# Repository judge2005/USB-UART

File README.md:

# USB-UART
A USB to serial adapter specifically designed for programming the ESP01. It uses node-mcu style programming, so no fiddling with buttons is necessary - just change the reset method to 'node-mcu'.

It has enough power to run the ESP01 without the need for an additional power source.

It uses the Silicon Labs CP2102N, so it can detect the charge protocol supported by the USB port it is plugged in to. You will have to use the Silicon Labs Express Configurator to set that up.

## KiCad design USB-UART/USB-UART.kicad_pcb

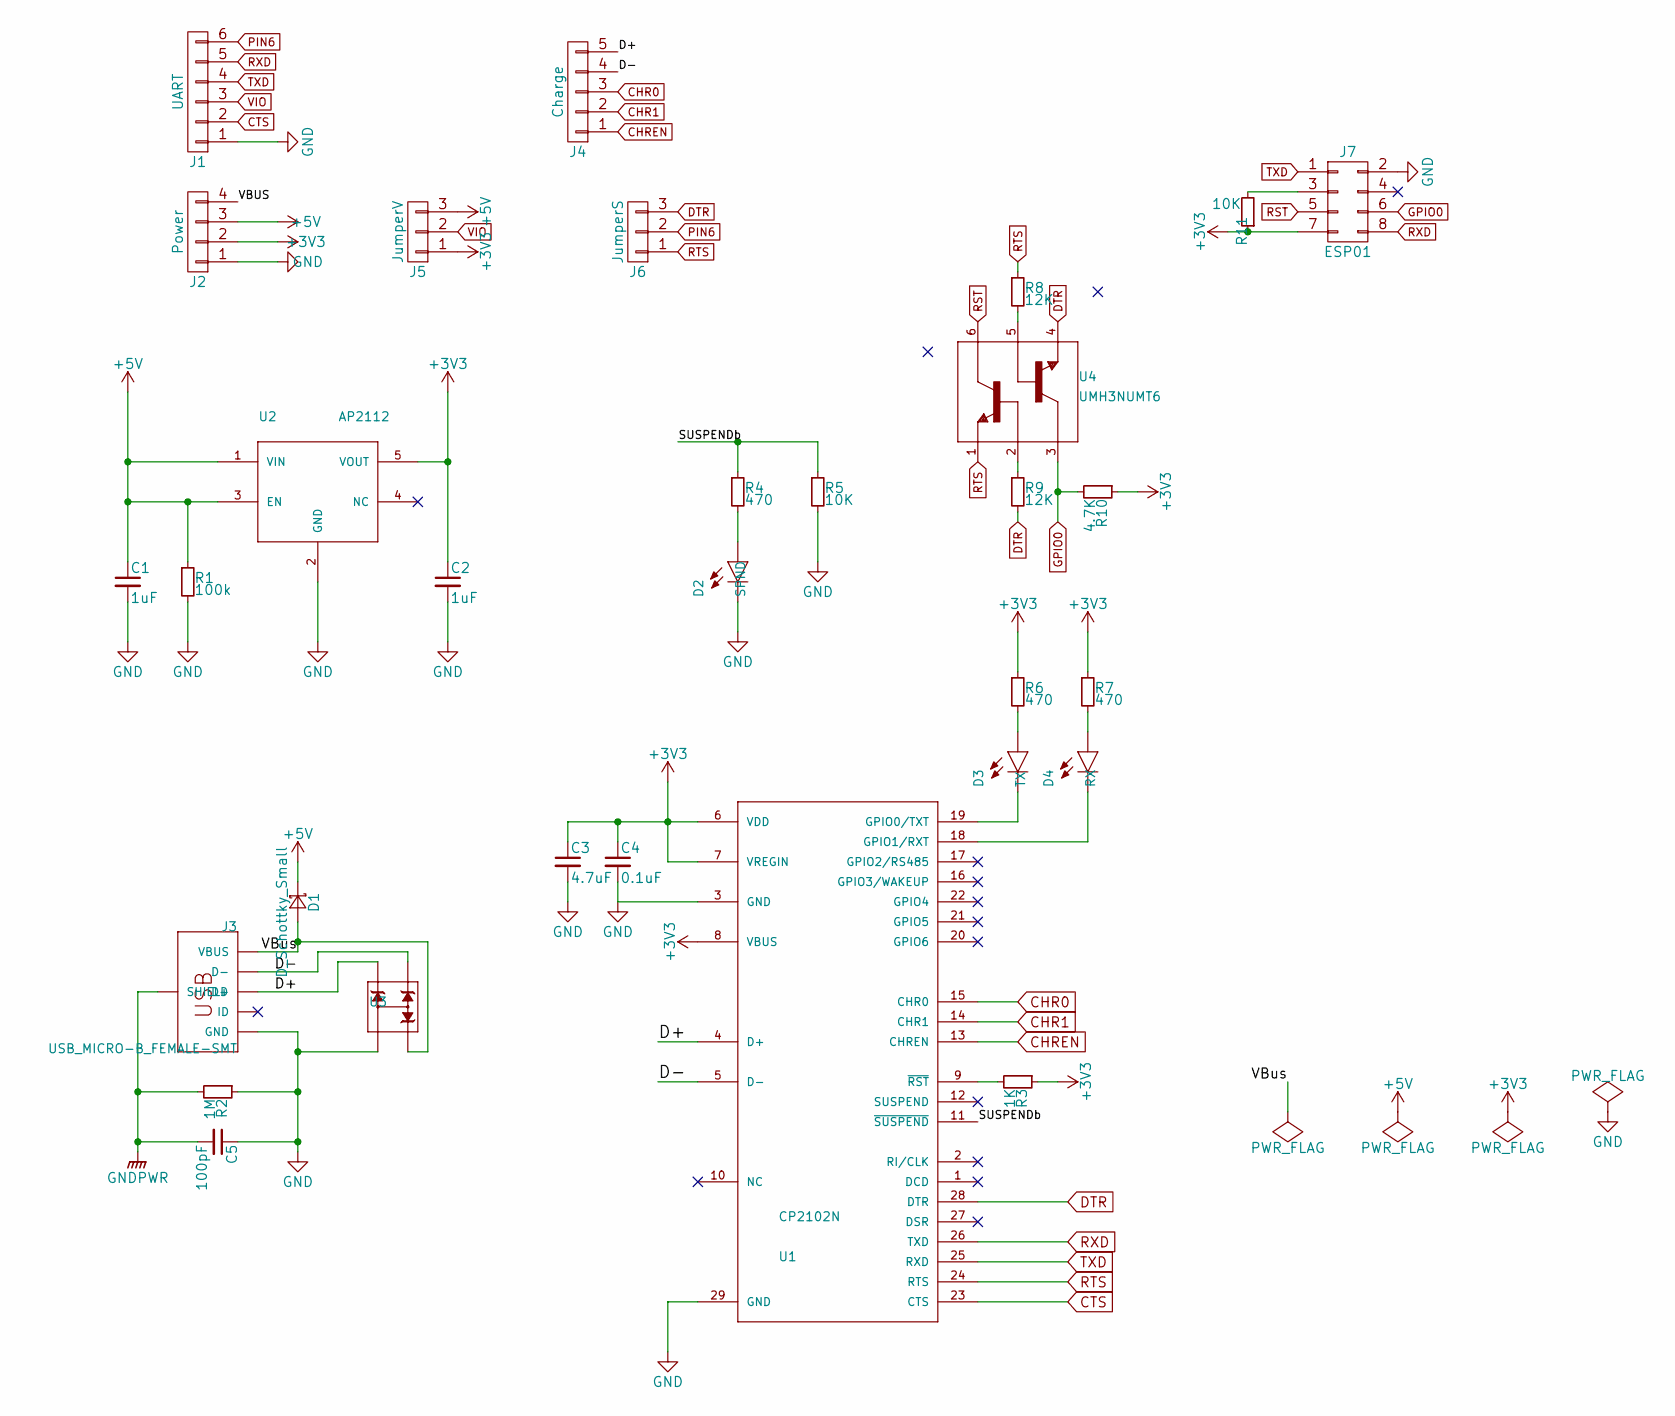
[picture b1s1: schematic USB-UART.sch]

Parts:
C1, C2: 1uF; SparkFun-Capacitors-0603
C3: 4.7uF; SparkFun-Capacitors-0603
C4: 0.1uF; SparkFun-Capacitors-0603
C5: 100pF; SparkFun-Capacitors-0603; Rating 1KV
D1: D_Schottky_Small; D_SOD-323_HandSoldering
D2: SPND; SparkFun-LED-LED-0603
D3: TX; SparkFun-LED-LED-0603
D4: RX; SparkFun-LED-LED-0603
J1: UART; SparkFun-Connectors-1X06_NO_SILK
J2: Power; SparkFun-Connectors-1X04_NO_SILK
J3: USB_MICRO-B_FEMALE-SMT; SparkFun-Connectors-USB-B-MICRO-SMD
J4: Charge; SparkFun-Connectors-1X05_NO_SILK
J5: JumperV; SparkFun-Connectors-1X03_NO_SILK
J6: JumperS; SparkFun-Connectors-1X03_NO_SILK
J7: ESP01; Socket_Strip_Straight_2x04_Pitch2.54mm
R1: 100k; SparkFun-Resistors-0603
R2: 1M; SparkFun-Resistors-0603
R3: 1K; SparkFun-Resistors-0603
R4, R6, R7: 470; SparkFun-Resistors-0603
R5, R11: 10K; SparkFun-Resistors-0603
R8, R9: 12K; SparkFun-Resistors-0603
R10: 4.7K; SparkFun-Resistors-0603
U1: CP2102N; nixiemisc-QFN28G_0.5-5X5MM
U2: AP2112; nixiemisc-SOT25
U3: ESD; nixiemisc-SOT143
U4: UMH3NUMT6; nixiemisc-UMT6

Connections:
+3V3: C2.1, C3.1, C4.1, J2.2, J5.1, J7.7, R3.1, R6.1, R7.1, R10.1, R11.1, U1.6 (VDD), U1.7 (VREGIN), U1.8 (VBUS), U2.5 (VOUT)
+5V: C1.1, D1.1 (K), J2.3, J5.3, R1.1, U2.1 (VIN), U2.3 (EN)
/D+: J3.D+, J4.5, U1.4 (D+), U3.4
/D-: J3.D-, J4.4, U1.5 (D-), U3.3
/SUSPENDb: R4.1, R5.1, U1.11 (~SUSPEND~)
/VBUS: D1.2 (A), J2.4, J3.VBUS, U3.2
CHR0: J4.3, U1.15 (CHR0)
CHR1: J4.2, U1.14 (CHR1)
CHREN: J4.1, U1.13 (CHREN)
CTS: J1.2, U1.23 (CTS)
DTR: J6.3, R9.2, U1.28 (DTR), U4.4 (E2)
GND: C1.2, C2.2, C3.2, C4.2, C5.1, D2.C, J1.1, J2.1, J3.GND, J7.2, R1.2, R2.1, R5.2, U1.3 (GND), U1.29 (GND), U2.2 (GND), U3.1
GNDPWR: C5.2, J3.SHIE (SHIELD), R2.2
GPIO0: J7.6, R10.2, U4.3 (C2)
unnamed: D2.A, R4.2
unnamed: D3.A, R6.2
unnamed: D3.C, U1.19 (GPIO0/TXT)
unnamed: D4.A, R7.2
unnamed: D4.C, U1.18 (GPIO1/RXT)
unnamed: J7.3, R11.2
unnamed: R3.2, U1.9 (~RST~)
unnamed: R8.2, U4.5 (B2)
unnamed: R9.1, U4.2 (B1)
PIN6: J1.6, J6.2
RST: J7.5, U4.6 (C1)
RTS: J6.1, R8.1, U1.24 (RTS), U4.1 (E1)
RXD: J1.5, J7.8, U1.26 (TXD)
TXD: J1.4, J7.1, U1.25 (RXD)
VIO: J1.3, J5.2

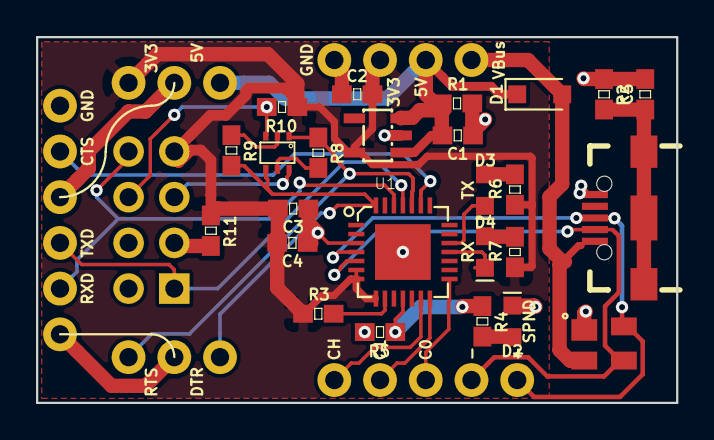
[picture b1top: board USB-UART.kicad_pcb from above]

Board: 2 copper layers, 35.6 x 20.3 mm, 31 parts (1 on the bottom side), 29 nets.
